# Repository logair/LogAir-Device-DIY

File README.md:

# Hardware docs for the DIY LogAir device

- Schematics
- PCB
- BoM
- Arduino code

The hardware as it is streams, once per second, the following data through BLE and to the uSD card:
Latitude, Longitude, Altitude, Speed, Heading, Temperature, Relative Humidity, Atmospheric Pressure, PM1, PM2.5, PM4, PM10

The Arduino-compatible MCU is a Bluepill, a generic implementation of the STM32F103. The chip is flashed with a code compiled with the Arduino IDE and the following libraries: NeoGPS, PMS Library, BME280, SdFat.

The data transmissio nprotocol is extensible to allow implementation of different sensors.

# How To

## Assemble
<details>
  <summary>Click to expand for instructions!</summary>
  
  ### Material

- LogAir PCB
- Bluepill + connectors
- BME280 + connector
- uSD module
- BLE module
- PMS7003 + connector
- DC step-up
- Charger module
- GPS module

- Soldering iron + tin
- double-sided tape + jelly tape if available
- cutting pliers
- flat pliers
  
  ### Instructions

0. A very first step should be to try and upload code to the Bluepill. This is before the rest as it happened that the chips could not be programmed, and realizing that after all that work is not ideal. Upload a bootloader, a blink code, and there you go.

1. Solder the Bluepill connectors. Use the holes in the PCB as a guide for alignment. The G (GND, ground) pins are harder to solder, because of the copper mass involved.
<div align="center"></div>

2. Solder the assembled Bluepill to the PCB. Pay attention to the orientation.
<div align=center></div>

3. Prepare the BME280 (solder the connectors), the BLE module (straighten the pins with a flat plier), and the uSD module
<div align=center></div>

4. Place the BLE, BME, and uSD modules. Follow the picture, the BME280 (violet module) should be as far as possible from the PCB), with its pins barely sticking through on the other side.
<div align=center></div>
<div align=center></div>

5. Prepare the PCB for the power modules: put a thin layer of tin on the (blue) charger module pads, and a solder blob on one of the (red) step-up pads
<div align=center></div>

6. Solder the charger module by putting it in place, and adding solder on the pads from the top. I count about 5 seconds of applying heat for the tin applied on step 5 to melt. Then solder the step-up module using the first pad to hold it in place. When you are done, check the conductivity between the pins of the two modules, and that between the pads of the charging module. The latter because the method used to solder can produce 'tin overflows'. 
<div align=center></div>
<div align=center></div>

Then place and solder the switch. Here, try to apply a minimal amount of tin. As the other side of the pins will go against the PMS7003 which has a conductive casing, the pins should be cut or filed down, then taped over (two layers of normal, clear tape are enough)
<div align=center></div>
<div align=center></div>

7. Bend lightly the SWD pins of the Bluepill to give room for soldering the GPS wires
<div align=center></div>

8. Solder the GPS wires. The order is the same as their order on the GPS-side plug, you can use the PCB markings (5V is red) and pictures to help you. The wires should not go over each other at any point for the order to be preserved.
<div align=center></div>
<div align=center></div>

9. Solder the connector for the PMS7003. As the width of the Bluepill vary a bit, it is safer to solder it lightly 'bent' away from the bluepill. To do that, solder the pins that are on the far side from the Bluepill first, then plug the PMS7003 in to see how thing fit. Then remove and solder the rest. 5-10 degrees should do.
<div align=center></div>

10. For a smaller device, I cut most of the pins apparent on the back of the PCB to the top of the tin cone. Apply insulation on the pins, and this is important. I use a sticky, translucent, think tape I found on aliexpress. Any other ~1-2mm insulating material will easily do.
<div align=center></div>

11. Solder the battery wires to the charger module pads
<div align=center></div>

12. Before finalizing the assembly, write down the PMS7003 serial number somewhere, to track device quality :)
<div align=center></div>

13. And it is done :)
<div align=center></div>

  </details>
  
## Program

<details>
  <summary>Click to expand for programming instructions!</summary>
  
### Pre-requisites
- A Bluepill with functional bootload (e.g. generic_boot20_pc13.bin from https://github.com/rogerclarkmelbourne/STM32duino-bootloader
- Install Arduino IDE
- Install board definition:File > Preferences > Additional Boards Manager URLs: add the following URL to the list (empty by default):
  `https://github.com/stm32duino/BoardManagerFiles/raw/main/package_stmicroelectronics_index.json`
- Tools > Board > Boards Manager > Search 'STM32' > Install 'STM32 MCU based boards'
    
<details>
<summary>For older instructions using unofficial stm32duino core</summary>
  
- Install board definition:File > Preferences > Additional Boards Manager URLs: add the following URL to the list (empty by default):
`http://dan.drown.org/stm32duino/package_STM32duino_index.json`
- Tools > Board > Boards Manager > Search 'STM32' > Install 'STM32F1xx/GD32F1xx boards'
- Once done, close the Board Manager and Select the Board: Tools > Board > STM32F1 Boards (Arduino_STM32) > Maple mini
  
NO NEED TO FOLLOW THE CONFIGURE SECTION BELOW.
    
</details>
  
### Configure
  - Select the proper board:
  `Tools > Boards > STM32 Boards (selected from submenu) > Generic STM32F1 series`
  - Enable configurations we need:
    - `Tools > U(S)ART Support > Enabled (Generic 'Serial')`
    - `Tools > USB Support > CDC (Generic Serial supersedes U(S)ART)`
    - `Tools > Upload Method > Maple DFU Bootloader 2.0`

### Libraries
Install the following libraries from the Library Manager
Tools > Manage Libraries... 

- NeoGPS: Install, and replace the contents of `$HOME/Arduino/libraries/NeoGPS/src/GPSport.h` by:
```
#ifndef GPSport_h
#define GPSport_h

#define gpsPort Serial2
#define GPS_PORT_NAME "Serial2"
#define DEBUG_PORT Serial

#endif
```
- BME280 by Tyler Glenn
- PMS Library by Mariusz Kacki
  
## Connect, compile and upload
Let us now try and upload a quick code to test if all works...

- Open the Blink example, and add `#define LED_BUILTIN PC13` at the very beginning
- Select the Port: Tools > Port > ... (depends on your OS)
- Press the Compile and Upload arrow....

If the upload does not go through, this might be because the board cannot auto-reset with your computer.
To upload, you will need to manually reset by pressing the button you can see near where the GPS chip is stuck just before pressing the Compile arrow. It takes a bit of trial and error and some OS's need it while some others don't.

## Upload the LogAir code
Download the code from the repository, and follow the same process as above.

## Connect
UART parameters to connect to the serial monitor are the ones set in the code. The default is 112500, but 9600 was previously used.

## Troubleshoot

### Board appears in dmesg, but not in lsusb 
You might need to create a udev rules file
`/etc/udev/rules.d/45-bluepill.rules`
```
ATTRS{idVendor}=="1eaf", ATTRS{idProduct}=="0004", MODE="0666" SYMLINK+="maple", ENV{ID_MM_DEVICE_IGNORE}="1"
ATTRS{idVendor}=="1eaf", ATTRS{idProduct}=="0003", MODE="0666" SYMLINK+="maple", ENV{ID_MM_DEVICE_IGNORE}="1"
```
  </details>
  
## Use

<details>
  <summary>Click to expand for usage instructions!</summary>
  
### Turning ON / OFF
The switch onthe back of the device allows to turn the device on and off.

The red or green blinking light shows when the device is writing on the SD card. When the LED is ON, the device should not be turned OFF as it might corrupt the card.

### Blinking LEDs

The modules we use include LEDs of varying colors. Here are some useful informations you can get from them:

- Bluetooth LED (green or red), left side of the device: This LED is blinking if no phone is connected to the device, and stays on when a connection is active.
- GPS LED (blue and red):
  - The red LED shows the module is powered, and should always be on when the device runs. 
  - The blue LED is blinking when the module receives signals strong enough to get a 'fix', or know its position. This is important if you rely on the SD card only to record the measurements, i.e. if you're not using a smartphone to send your data to the server.
- Device LEDs:
  - Left LED: red or green, signals the controller receives power. Should always be ON when the device is turned on.
  - Right LED: red or green, currently parametered to signal the device is writing to the SD card and should not be powered off. You can turn the device OFF when the LED is OFF.

### With the LogAir APP
Follow the instructions on our video tutorial.

### Stand-alone
The LogAir device records its measurements on the micro-SD card, which can be extracted and imported into a spreadsheet or GIS program.

The limitation in this mode is that the device can only rely on its own GPS module for time and position. This means that, before a valid GPS signal is acquired, the measurements on the SD card will not list any time or position. 

The signal depends on your location, the time of the day, if there are obstacles between the device and the sky, etc. Indoor measurements are often difficult, but windowsills sometimes give good results.

We are trying to find a way to give the current time to the device by using a program on the computer, or preparing it on the SD card, but there is no easy solution there... See ToDos, input welcome :)

</details>

# ToDo

Here are several items that are planned, currently developed, or on hold pending contributions. If you are interested in any of them be it for giving a helping hand or advices, please get in touch :)
  
## Hardware

These items focus on the device conception, including electronics, casing, production, etc.

<details>
  <summary>Click to expand for Hardware development tasks!</summary>
  
- Disconnect PC14 and PC15 for RTC reliability
- Better power supply, as this one just charges and discharges blindly.
- Integrate the components on a printed circuit board
- Replace the BLE module with an ESP32 (the STM32 might have to stay, as ESP32 are more limited, e.g., available UARTs)
- Make a similar MVP with SPS30 & SHT3x
- Add a LoRa chip! See Clement's work
- ...

</details>

## Firmware

Firmware development focuses on the program that makes the device run. The brain within the machine :)

<details>
  <summary>Click to expand for Firmware development tasks!</summary>

- Provide a time base when no GPS signal is present, and no phone is connected
  - Implement RTC (there is an on-board crystal on the Bluepill).
  - Implement time input from serial (BLE and/or PC)
- Implement better data storage and upload 
  - Log data with human-readable time as well as UNIX timestamp
  - Revamp buffering to limit uSD write operations
  - Revamp data storage on the SD card (textfile + DB?)
  - Implement deferred data upload for when uplink not continuously available
- Implement online GPS config: some changes to the embedded GPS FW are sometimes necessary for best operation
  - Get and store almanach/ephemeris on uSD card! This would really help with no-phone collection
  - Other generic config, constellations, accuracy requirements, etc.
- Implement component recognition: find out which sensors are used from their output stream (starting with PM sensor)
- Add interrupts everywhere?
- ...

</details>

## APP

Here, developmetn of our application that helps collect and send data from the device to the servers, and get it back in forms of maps, messages, etc. Our UI sucks? Contribute a better one ;)

<details>
  <summary>Click to expand for APP development tasks!</summary>
  
- All 
  - Implement API key for upload/download

- Android version
  - APP should check at startup that GPS is enabled (and available in background if knowable) and prompt if not. 
  - Make it simpler: no settings, sending all packets stored every 10sec, etc
  - Auto-connect: priority to previously connected devices, then to '.*logair.*', etc
  - Map should be loaded at startup, not only when map tab is opened
  - ...

- iOS version
  - Make one :x Nicos is on it!
  - ...

</details>

## Backend

All the work that helps gather the data, safekeep it, develop ways to use it, share it, etc. DBs, services, APIs and the like. Put your hoodie on and hack away!

<details>
  <summary>Click to expand for Backend development tasks!</summary>
  
  - Implement API key for upload/download
  - ...

</details>

## Data

All the work that develop ways to analyse, understand and use the data. Algorithms, GIS, dashboards etc.

 <details>
  <summary>Click to expand for Data visualisation and Data science tasks!</summary>
  
  - Make a dashboard! 
  - Build a QGIS server that works fast enough
  - Find missing data points in the contributions, and signal them for collection
  - Find periods in the signal, and exploit them
  - Build a better pipeline for extraction and analysis

</details>

# Upcoming

- Arduino library configs
- ToDo list updates
- Assembly instructions (video?)

Licensed under [CERN OHL v.1.2 or later](https://ohwr.org/project/cernohl/wikis/home)

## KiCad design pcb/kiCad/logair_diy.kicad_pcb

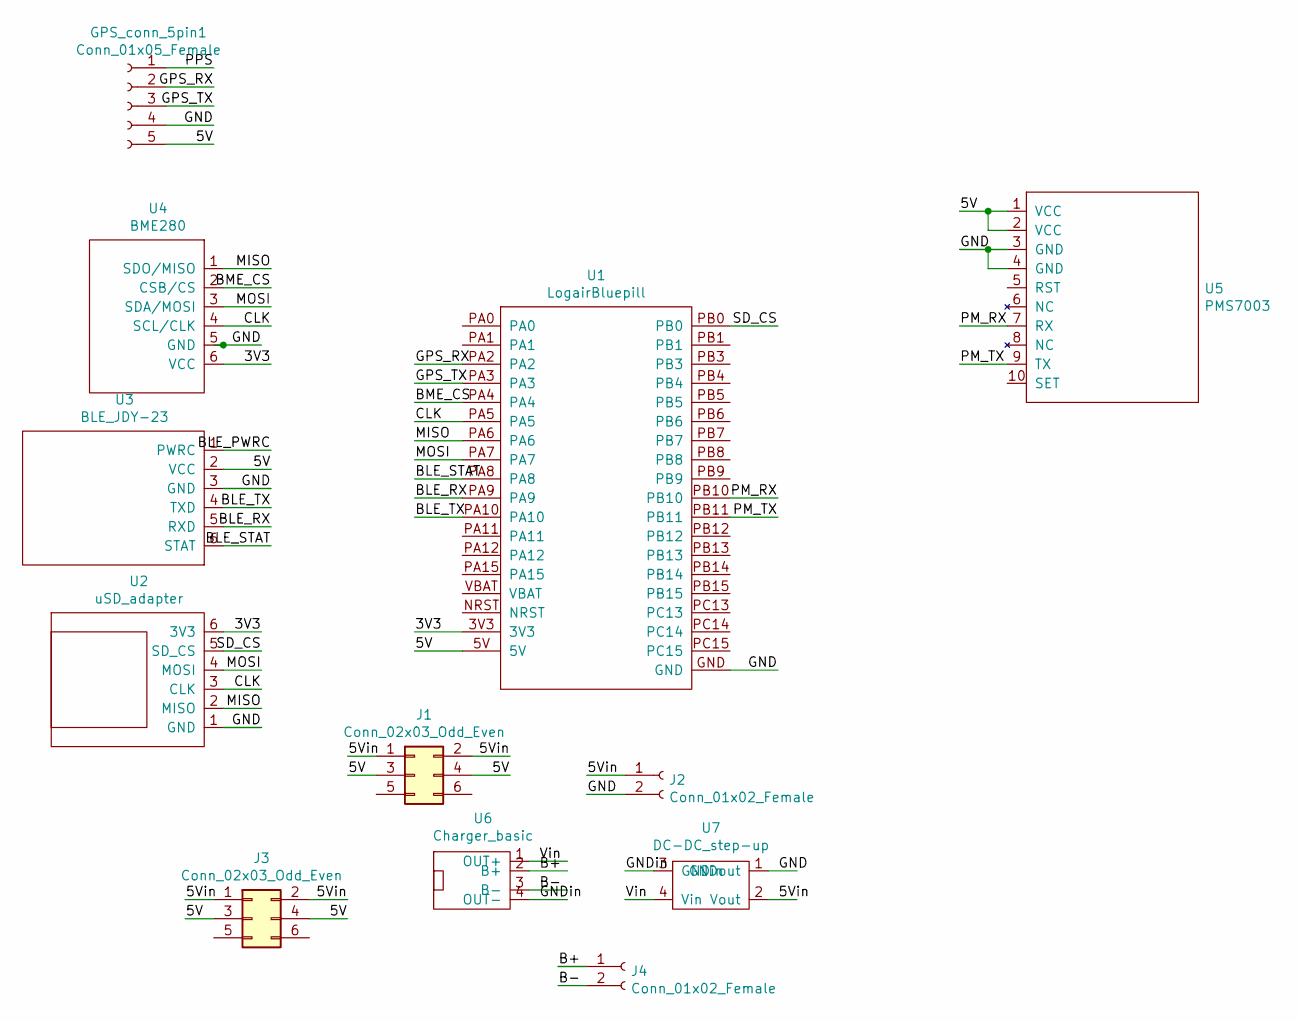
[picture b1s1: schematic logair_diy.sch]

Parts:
GPS_conn_5pin1: Conn_01x05_Female; PinHeader_1x05_P2.54mm_Vertical
J1: Conn_02x03_Odd_Even; PinHeader_2x03_P2.54mm_Vertical
J2, J4: Conn_01x02_Female; PinSocket_1x02_P2.54mm_Vertical
J3: Conn_02x03_Odd_Even; Logair_switch_2
U1: LogairBluepill
U2: uSD_adapter
U3: BLE_JDY-23; BLE_JDY-23_vert_unfold
U4: BME280; BME280_SPI
U5: PMS7003; PMS7003_10pin
U6: Charger_basic
U7: DC-DC_step-up; DC-DC step-up

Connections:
/3V3: U1.3V3, U2.6 (3V3), U4.6 (VCC)
/5V: GPS_conn_5pin1.5, J1.3, J1.4, J3.3, J3.4, U1.5V, U3.2 (VCC), U5.1 (VCC), U5.2 (VCC)
/5Vin: J1.1, J1.2, J2.1, J3.1, J3.2, U7.2 (Vout)
/B+: J4.1, U6.2 (B+)
/B-: J4.2, U6.3 (B-)
/BLE_PWRC: U3.1 (PWRC)
/BLE_RX: U1.PA9, U3.5 (RXD)
/BLE_STAT: U1.PA8, U3.6 (STAT)
/BLE_TX: U1.PA10, U3.4 (TXD)
/BME_CS: U1.PA4, U4.2 (CSB/CS)
/CLK: U1.PA5, U2.3 (CLK), U4.4 (SCL/CLK)
/GND: GPS_conn_5pin1.4, J2.2, U1.GND, U2.1 (GND), U3.3 (GND), U4.5 (GND), U5.3 (GND), U5.4 (GND), U7.1 (GNDout)
/GNDin: U6.4 (OUT-), U7.3 (GNDin)
/GPS_RX: GPS_conn_5pin1.2, U1.PA2
/GPS_TX: GPS_conn_5pin1.3, U1.PA3
/MISO: U1.PA6, U2.2 (MISO), U4.1 (SDO/MISO)
/MOSI: U1.PA7, U2.4 (MOSI), U4.3 (SDA/MOSI)
/PM_RX: U1.PB10, U5.7 (RX)
/PM_TX: U1.PB11, U5.9 (TX)
/PPS: GPS_conn_5pin1.1
/SD_CS: U1.PB0, U2.5 (SD_CS)
/Vin: U6.1 (OUT+), U7.4 (Vin)

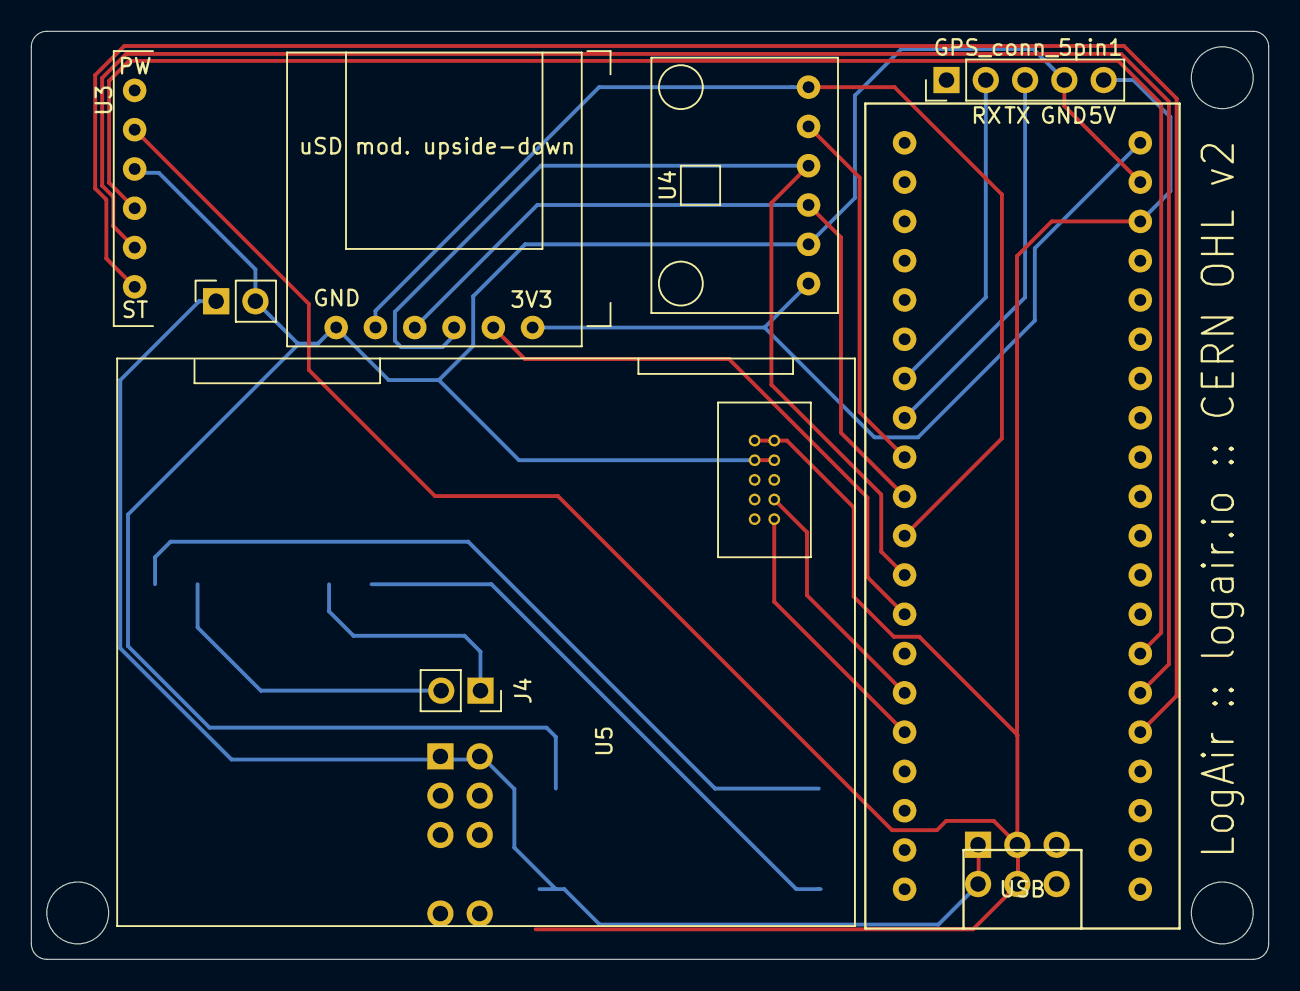
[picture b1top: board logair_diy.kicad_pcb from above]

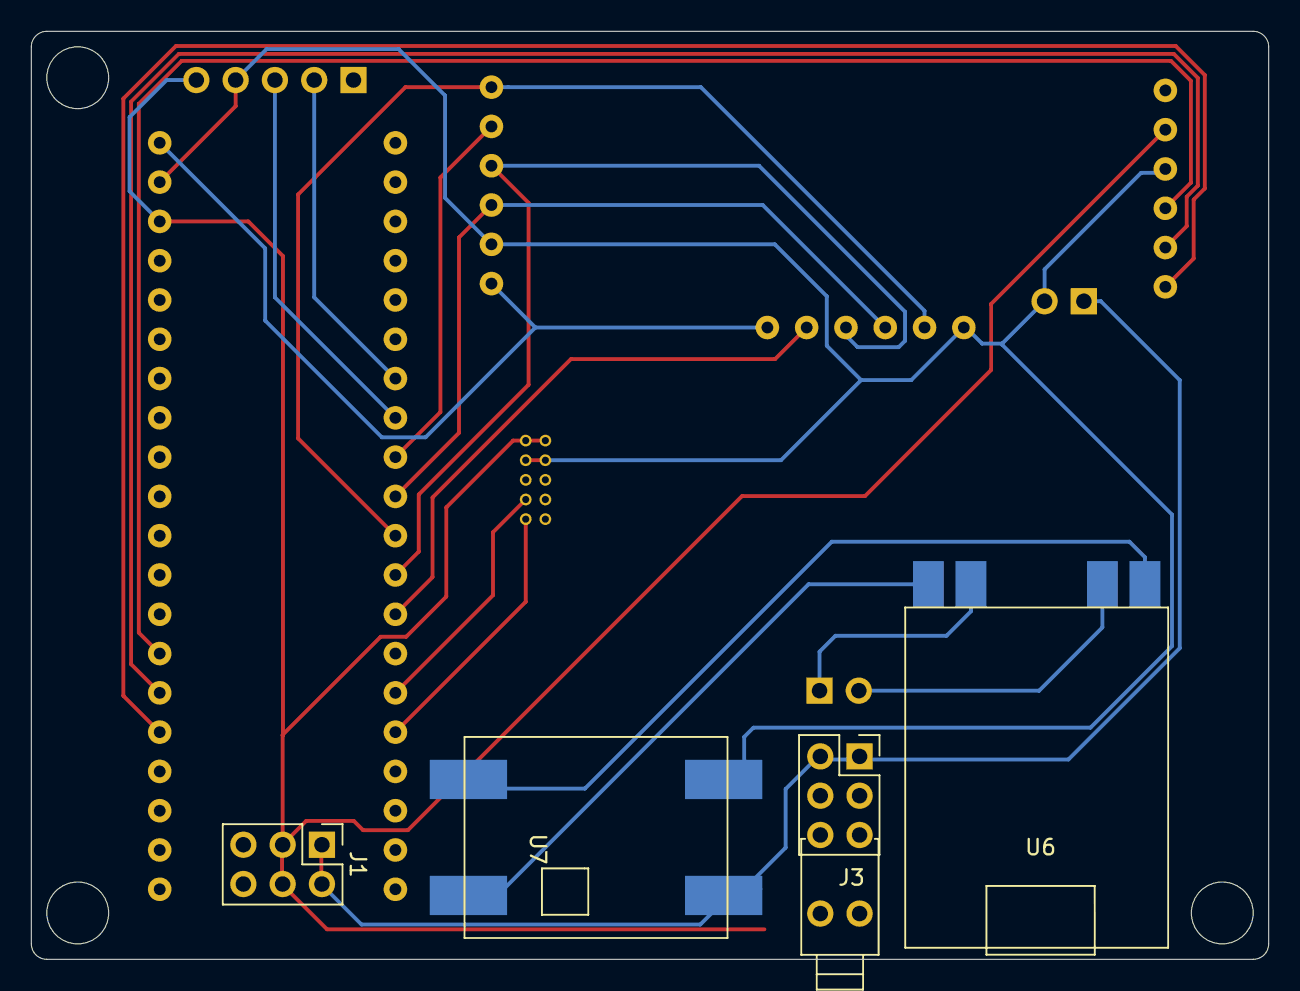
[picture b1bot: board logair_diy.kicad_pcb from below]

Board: 2 copper layers, 80.0 x 60.0 mm, 12 parts (4 on the bottom side), 20 nets.

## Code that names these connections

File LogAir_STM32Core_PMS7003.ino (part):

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#define USB_SERIAL 115200

// SPI device pin definition
#define DEVICE_PIN PA4

// LED pin and status definition
#define LED_BUILTIN PC13 // User LED pin definition
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HardwareSerial SerialX( RX, TX)
*/
//HardwareSerial Serial1(PB7,PB6);
HardwareSerial Serial2(PA3,PA2);
HardwareSerial Serial3(PB11,PB10);

int battery;

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int connected = 0;
int header_step = 10;

const uint8_t SDChipSelect = PB0; // SD Chip Select pin



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{

  pinMode(LED_BUILTIN, OUTPUT);
  pinMode(PA8, INPUT);
  Serial.begin( USB_SERIAL ); // USB Serial

  SPI.begin();
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    Serial1.println(header);
    Serial.println(header);

    if (digitalRead(PA8)){
      Serial.println("Connected");
    } else {
      Serial.println("Not Connected");
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
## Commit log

2020-08-27 Remove LoRa, add PCB
2020-10-23 Adding schematics and pcb
2021-10-15 add pcb file form kicad
2021-10-21 Adding ToDo's
2021-10-21 Update README.md
    HowTo's for install, config and connection
2021-10-21 Update README.md
    udev rules in case
2021-10-22 General update
2021-10-25 Adding assembly instruction pictures
2021-10-25 Lighter images
2021-10-25 Adding instructions
2021-10-25 Adding assembly instructions
2021-10-25 structure
2021-10-25 update structure
2021-10-26 Adding new STM32 Core
2021-10-26 Renaming for future
2021-10-26 adding one
2021-10-26 Auto-config for bluetooth and GPS module
2021-10-26 Clarification on serial speed
2021-11-29 Adding more explicit instructions

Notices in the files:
LogAir_STM32Core_PMS7003.ino:
Copyright (C) 2017-2021, Emmanuel Kellner
pcb/kiCad/logair_diy.kicad_pcb:
LogAir :: logair.io :: CERN OHL v2
